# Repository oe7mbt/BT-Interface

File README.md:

Bluetooth Adpapter für AprsDroid

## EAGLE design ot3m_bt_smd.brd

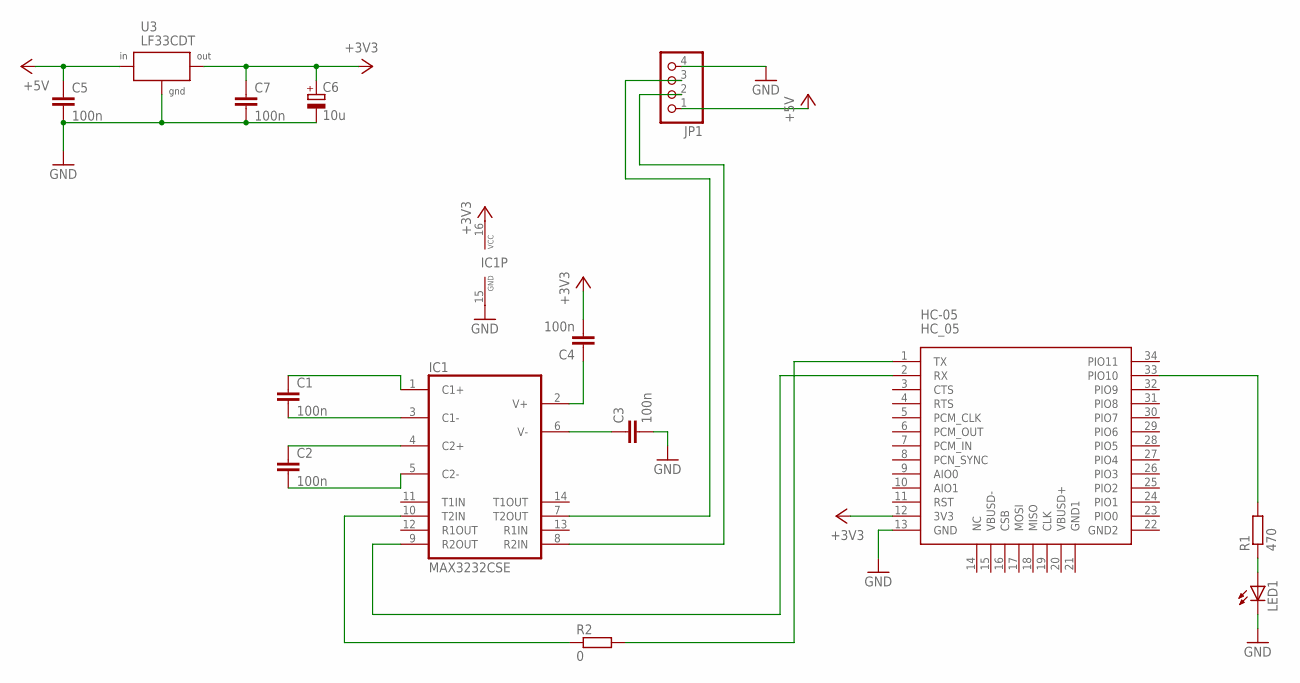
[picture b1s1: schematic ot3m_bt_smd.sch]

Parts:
C1, C2, C3, C4, C5, C7: 100n; C0805
C6: 10u; PANASONIC_B
HC-05: HC_05; BLUETOOTH_SMD
IC1: MAX3232CSE; SO16
JP1: PINHD-1X4/90; 1X04/90
LED1: LEDCHIP-LED0805; CHIP-LED0805
R1: 470; M0805
R2: 0; M0805
U3: LF33CDT; DPACK

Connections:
+3V3: C4.2, C6.+, C7.1, HC-05.12 (3V3), IC1.16 (VCC), U3.3 (OUT)
+5V: C5.1, JP1.1, U3.1 (IN)
GND: C3.2, C5.2, C6.-, C7.2, HC-05.13 (GND), IC1.15 (GND), JP1.4, LED1.C, U3.2 (GND)
unnamed: C1.1, IC1.1 (C1+)
unnamed: C1.2, IC1.3 (C1-)
unnamed: C2.1, IC1.4 (C2+)
unnamed: C2.2, IC1.5 (C2-)
unnamed: C4.1, IC1.2 (V+)
unnamed: C3.1, IC1.6 (V-)
unnamed: HC-05.1 (TX), R2.2
unnamed: HC-05.33 (PIO10), R1.2
unnamed: HC-05.2 (RX), IC1.9 (R2OUT)
unnamed: IC1.7 (T2OUT), JP1.3
unnamed: IC1.10 (T2IN), R2.1
unnamed: LED1.A, R1.1
unnamed: IC1.8 (R2IN), JP1.2

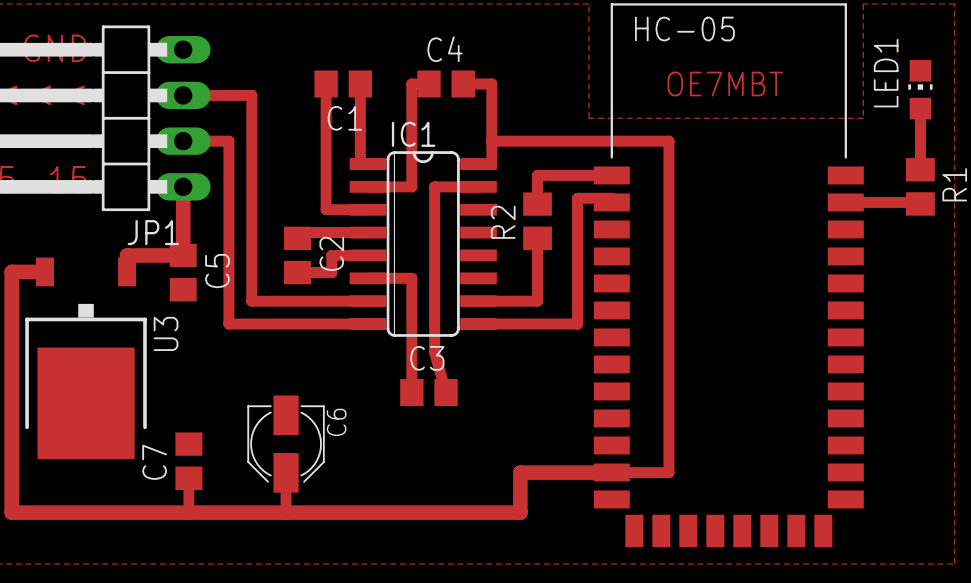
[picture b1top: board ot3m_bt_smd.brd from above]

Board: 2 copper layers, 14 parts (0 on the bottom side), 16 nets.

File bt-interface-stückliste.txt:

Partlist

Exported from ot3m_bt_smd.sch at 18.06.2015 00:50:07

EAGLE Version 7.1.0 Copyright (c) 1988-2014 CadSoft

Assembly variant: 

Part     Value          Device          Package       Library             Sheet

C1       100n           C-EUC0805       C0805         rcl                 1
C2       100n           C-EUC0805       C0805         rcl                 1
C3       100n           C-EUC0805       C0805         rcl                 1
C4       100n           C-EUC0805       C0805         rcl                 1
C5       100n           C-EUC0805       C0805         rcl                 1
C6       10u            CPOL-EUB        PANASONIC_B   resistor            1
C7       100n           C-EUC0805       C0805         rcl                 1
HC-05    HC_05          HC_05           BLUETOOTH_SMD Bluetooth HC-05     1
IC1      MAX3232CSE     MAX3232CSE      SO16          maxim               1
JP1                     PINHD-1X4/90    1X04/90       pinhead             1
LED1                    LEDCHIP-LED0805 CHIP-LED0805  led                 1
R1       470            R-EU_M0805      M0805         rcl                 1
R2       0              R-EU_M0805      M0805         rcl                 1
U3       LF33CDT        LF33_TO252      DPACK         power_stabilizators 1
